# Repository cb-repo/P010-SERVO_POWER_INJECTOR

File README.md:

# SERVO POWER INJECTOR (SPI) / BATTERY ELIMINATOR CIRCUIT (BEC) - v2.0

SERVO POWER INJECTOR (SPI) is a twist on the standard Battery Eliminator Circuit (BEC), providing the expected light-weight high-current power supply functionality while adding the option to splice a control signal directly into a standard servo connector.

This functionality means this SPI/BEC product can operate in 2 distinct modes. 
1. Standard BEC Mode: Providing a stable 5V or 9V output voltage for any requiring electronc, such as radios.
2. Power Injector Mode: Includes the same 5V/9V power output but also integrates the SIG pin. Now passing the signal from the input pad and injecting it into the standard factory servo connector output. Useful for powering and connecting signals to servos and ESC inputs without modification of the factory connectors.

This is a [New Zealand](https://www.google.co.nz/maps/place/Christchurch+New+Zealand) based product by [cb-technology](https://www.cb-technology.co.nz/), Connor Benton.

## FEATURES

- Small form-factor and lightweight design to be easily substituted into any new or exiting systems.
- Selectable 5V or 9V voltage outputs.
- Wide input voltage range.
- High current rating to allow reliable operation when powering hobby servo's.
- Inline connection layout (IN one side OUT the other)
- Integrated thermal and current limiting.
- Red power LED to display arming of downstream electronics.
- Signal track protection. Small series resistor added to the signal track to minimise cascading failures in-case of a fault downstream.

## SPECIFICATIONS
- **Dimensions:** 10x16x4 mm
- **Weight:** 3g
- **Voltage Input:** 6-33.6 V (2-8S LiPo)
- **Voltage Output:** 5V *default* (9V *selectable*)
- **Current - Rated:** 3.5 A
- **Current - Max:** 5 A
- **Connector Input:** Solder Pads
- **Connector Output:** Solder Pads or 3-pin Pin Header (Standard Servo Connector)

## CONNECTION DIAGRAM

### Mode: Standard BEC

### Mode: Servo Power Injector

## OUTPUT VOLTAGE SELECTION

On the underside of the board there are two adjacent cemicircular pads beside the label *9V(5Vdef)* which control the output voltage.

### 5V

Leave pads unsoldered (default from factory)

### 9V

Use a soldering iron to bridge pads with solder

## SERVO CONNECTOR ORIENTATION

When soldering the 3-pin Pin Header for use with a servo ther are 4 orientations that work with the privided right angle header

### Connector Orientation 1

### Connector Orientation 2

### Connector Orientation 3

### Connector Orientation 4

## DISCLIAMER

This product, and all other cb-technology products, are intended for use in hobby projects, and for educational and experimental uses. These devices are not suitable for any application where human life or health or significant property value depend on their proper operation. cb-technology ltd are not responsible for any loss or damage incurred by the operation or failure of this product or any others. The specifications listed are accurate to the best of our knowledge but are not guaranteed in any way. The buyer assumes all responsibility for proper use, testing, and verification of this unit in any application. cb-technology ltd liability is limited to replacement of defective DOA units. By installing and using this unit you are agreeing to these terms. If you do not agree you may return any unused units for a refund.

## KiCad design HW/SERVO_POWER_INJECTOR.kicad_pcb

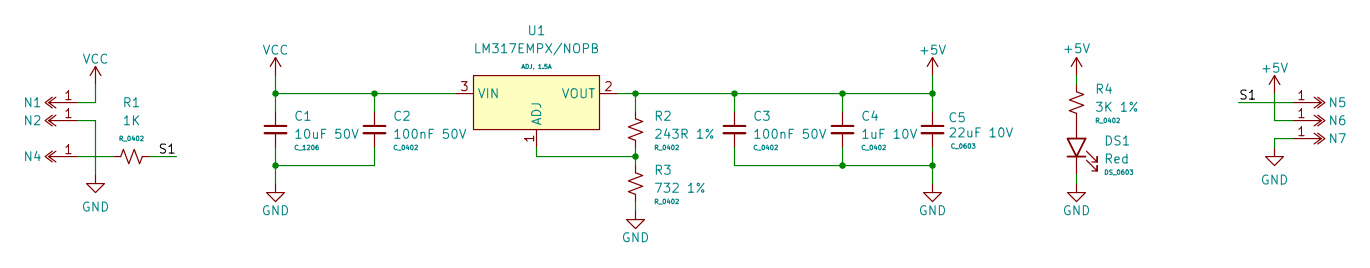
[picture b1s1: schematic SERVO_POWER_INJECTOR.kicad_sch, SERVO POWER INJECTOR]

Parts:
C1: 10uF 50V; C_1206; MFG Part FCC1206X106K500HT; LCSC Part C7467044
C2, C3: 100nF 50V; C_0402; MFG Part FCC0402B104K500AT; LCSC Part C5137492
C4: 1uF 10V; C_0402; MFG Part FCC0402X105K100AT; LCSC Part C5137473
C5: 22uF 10V; C_0603; MFG Part CL10A226MP8NUNE; LCSC Part C86295
DS1: Red; DS_0603; MFG Part XL-1608SURC-06; LCSC Part C965799
N1, N2, N4, N5, N6, N7: Finger_2.5x4_M1
R1: 1K; R_0402
R2: 243R 1%; R_0402; MFG Part FRC0402F2430TS; LCSC Part C2929995
R3: 732 1%; R_0402; MFG Part RC0402FR-07732RL; LCSC Part C137939
R4: 3K 1%; R_0402; MFG Part FRC0402F3001TS; LCSC Part C2909355
U1: LM317EMPX/NOPB; SOT223_3

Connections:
+5V: C3.1, C4.1, C5.1, N6.1, R2.1, R4.1, U1.2 (VOUT)
/S1: N5.1, R1.2
GND: C1.2, C2.2, C3.2, C4.2, C5.2, DS1.1 (K), N2.1, N7.1, R3.2
unnamed: DS1.2 (A), R4.2
unnamed: N4.1, R1.1
unnamed: R2.2, R3.1, U1.1 (ADJ)
VCC: C1.1, C2.1, N1.1, U1.3 (VIN)

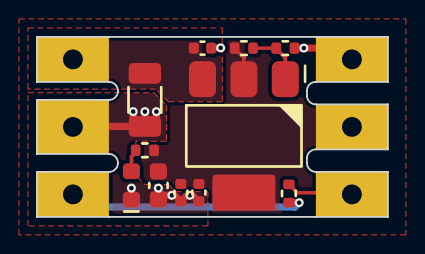
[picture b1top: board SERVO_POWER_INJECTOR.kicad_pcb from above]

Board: 2 copper layers, 19.5 x 10.0 mm, 17 parts (0 on the bottom side), 7 nets.

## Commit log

2022-07-04 Initialise LFS in Repo
2022-07-07 Generate first revision servo power injector
2022-07-24 Update Readme for release to CRNZ
2022-08-01 Update product description to include BEC
2022-08-09 Update README to include BEC info
2023-10-17 Add Packaging Label to Repo
2024-09-12 WIP Commit
2025-02-23 Add Assets and Create README for SPI/BEC v1.0
2025-02-23 Update Asset Links in README
2025-02-24 Update Connection Graphics
2025-02-24 Update Asset Image Path
2025-03-07 Update README with Updated Asset Photos
2025-05-21 Update Datatsheet to standardize with other products
2025-05-21 Update SPI/BEC Image
2025-05-21 More Minor Formatting Changes
